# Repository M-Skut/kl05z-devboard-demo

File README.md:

# KL-05 DevBoard Demo project with simple HAL

## Hardware
To make development of advanced microcontroller projects simple, the DevBoard is equipped with following features:
- SD Card slot
- 6-button keypad connected as analog input
- stylophone-like keyboard as analog input
- PMOD Interface Type 2 (SPI)
- MikroBus Connector
- 3x WS2812B addressable RGB LEDs
- connector for Nokia 5510 display board
- buzzer
- fused 3V3 and 5V lines
- connector for Adafruit ALS-PT19 Analog Light Sensor Breakout
- connector for 16x2 LCD with I2C adapter
- 25LCxxx SPI Flash
- 2x 24Cxx I2C Flash
- RTC clock with battery based on PCF8563 RTC IC with I2C interface
- LM75 I2C temperature sensor

## Some photos of the hardware (more in `media` folder)

## Bill Of Materials
Interactive Bill Of Materials for the newest revision of the hardware can be found [here](frdm05-devboard-hardware/bom/ibom.html)

#### Hardware revision history
Rev. 1:
- first revision of hardware
Rev. 2:
- fix for analog keypad (wrong placement of current mirror)
- addition of current-limiting resistor for buzzer
- addition of optional fuses for 3V3 and 5V lines
Rev. 2.1:
- fix for 3V3 fuse
- fix for buzzer footprint
- fix for some silkscreen areas
Rev. 2.2:
- change 74HCT1G125GV buffer to faster 74AHCT1G125GV version

## Environment
To develop this demonstration project, following set of tools and programs was used:
- [Visual Studio Code](https://code.visualstudio.com/) with plugins:
    - [`Cortex Debug`](https://marketplace.visualstudio.com/items?itemName=marus25.cortex-debug) from `marus25`
    - [`CMake Tools`](https://marketplace.visualstudio.com/items?itemName=ms-vscode.cmake-tools) from `microsoft`
- GNU GCC ARM Compiler from Official ARM Distribution
- SEGGER JLINK
- CMake
- Ninja
- (Optional) ARM Compiler 5 from Keil
- (Optional) Doxygen

### How to install it on Windows
- Install GCC from [Official ARM Distribution](https://developer.arm.com/tools-and-software/open-source-software/developer-tools/gnu-toolchain/gnu-rm/downloads) and **check "Add to PATH"** when installing
- Install [CMake](https://cmake.org/download/), also **Add to PATH** when installing
- Install [J-Link Software and Documentation pack](https://www.segger.com/downloads/jlink/)
- Download [Ninja](https://github.com/ninja-build/ninja/releases) and put it into some folder in PATH, for example in `C:\Program Files\CMake\bin`
- [Install Visual Studio Code](https://code.visualstudio.com/download) and its extensions
- (Optional) Install [Doxygen](https://www.doxygen.nl/download.html) for generating documentation

### How to install it on other operating systems
- Install the required software from author's website or from OS repositories.

Now you can open the project folder. Select GNU toolchain as CMake kit when asked and edit file `launch.json` inside `.vscode` folder if your `JLinkGDBServer` location is different than he one used in this project. For ARM Compiler 5.06 toolchain,
an environment variable `ARMCC_TOOLCHAIN_PATH` has to be set to `bin` folder of the toolchain files. Alternatively, `armcc.cmake` file inside `toolchain-conf` can be edited to make te path setting permanent.

### Environment features
- two-click switch between ARM Compiler 5 and GCC Compiler
- all code editing features that Visual Studio Code has to offer
- easy debugging of compiled code
- two-click generation of doxygen HTML documentation
- built-in git integration
- works on Windows, GNU/Linux and Mac OS (or at least should)

## HAL
This simple hardware abstraction layer is based on two sources: KL05 Sample Code Package
from Freescale and MBED platform-specific code for KLXX targets. The C API relies
on heavy use of custom enums and structs to ensure that invalid function parameters can be found in
compilation stage. It uses C99 features (`stdint.h`, `stdbool.h`, in-place struct 
initialization etc.) and was tested with GCC 11 compiler and ARM 5.06 Compiler, but should
be compiler-independent, as it does not use compiler-dependent features directly, but instead it's using
CMSIS functions as abstraction layer.

### Goals:
- Prevent user from error-prone and hard-to-debug manual peripheral register setting
- Simple and straightforward for both understanding the underlying code and using the API
- Versatile - use for all applications within this uC
- Smallish footprint
- Separated device drivers from mcu peripheral drivers (exceptions only for very timing-sensitive devices)
- User-proof, mostly
- Peripherals can be reinitialized and will still work
- Communication peripheral drivers can be used without gpio driver
- Supports any MCU working frequency 

### Non-goals:
- universal
- unified (in GPIO mapping, same peripheral but more instances etc.)

### Drivers features:
#### UART:
- different pinout configuration
- automatic calculation for baudrate with ability to re-init if CPU speed changes
- error if configuration baudrate or pins cannot be set
- simple print, putchar and getchar API
- RX IRQ callback setting and checking RX overrun

#### I2C:
- different pinout configuration
- different speed selection
- timeout detection in all functions
- included fix for silicon errata
  
#### GPIO
- bare-bones abstraction of the register setting
- interrupt with callback functions
- inline functions for fast pin setting

#### Delay
- SysTick-based delay
- works without affecting SysTick settings
- based on delay code from u8g2 project

#### ADC
- ADC calibration function
- simple 16-bit value read
- uses `gpio` driver for pin mapping
- ADC presets (currently only one available)

#### PWM
- TPM-based PWM
- uses `gpio` driver for pin mapping
- allows setting period and pulse width in microseconds or as raw values

#### WS2812
- currently only GCC supported
- based on [cpldcpu's WS2812 ARM bitbang driver](https://github.com/cpldcpu/light_ws2812/blob/master/light_ws2812_ARM/light_ws2812_cortex.c)

#### MMA8451Q
- range setting
- conversion to float values

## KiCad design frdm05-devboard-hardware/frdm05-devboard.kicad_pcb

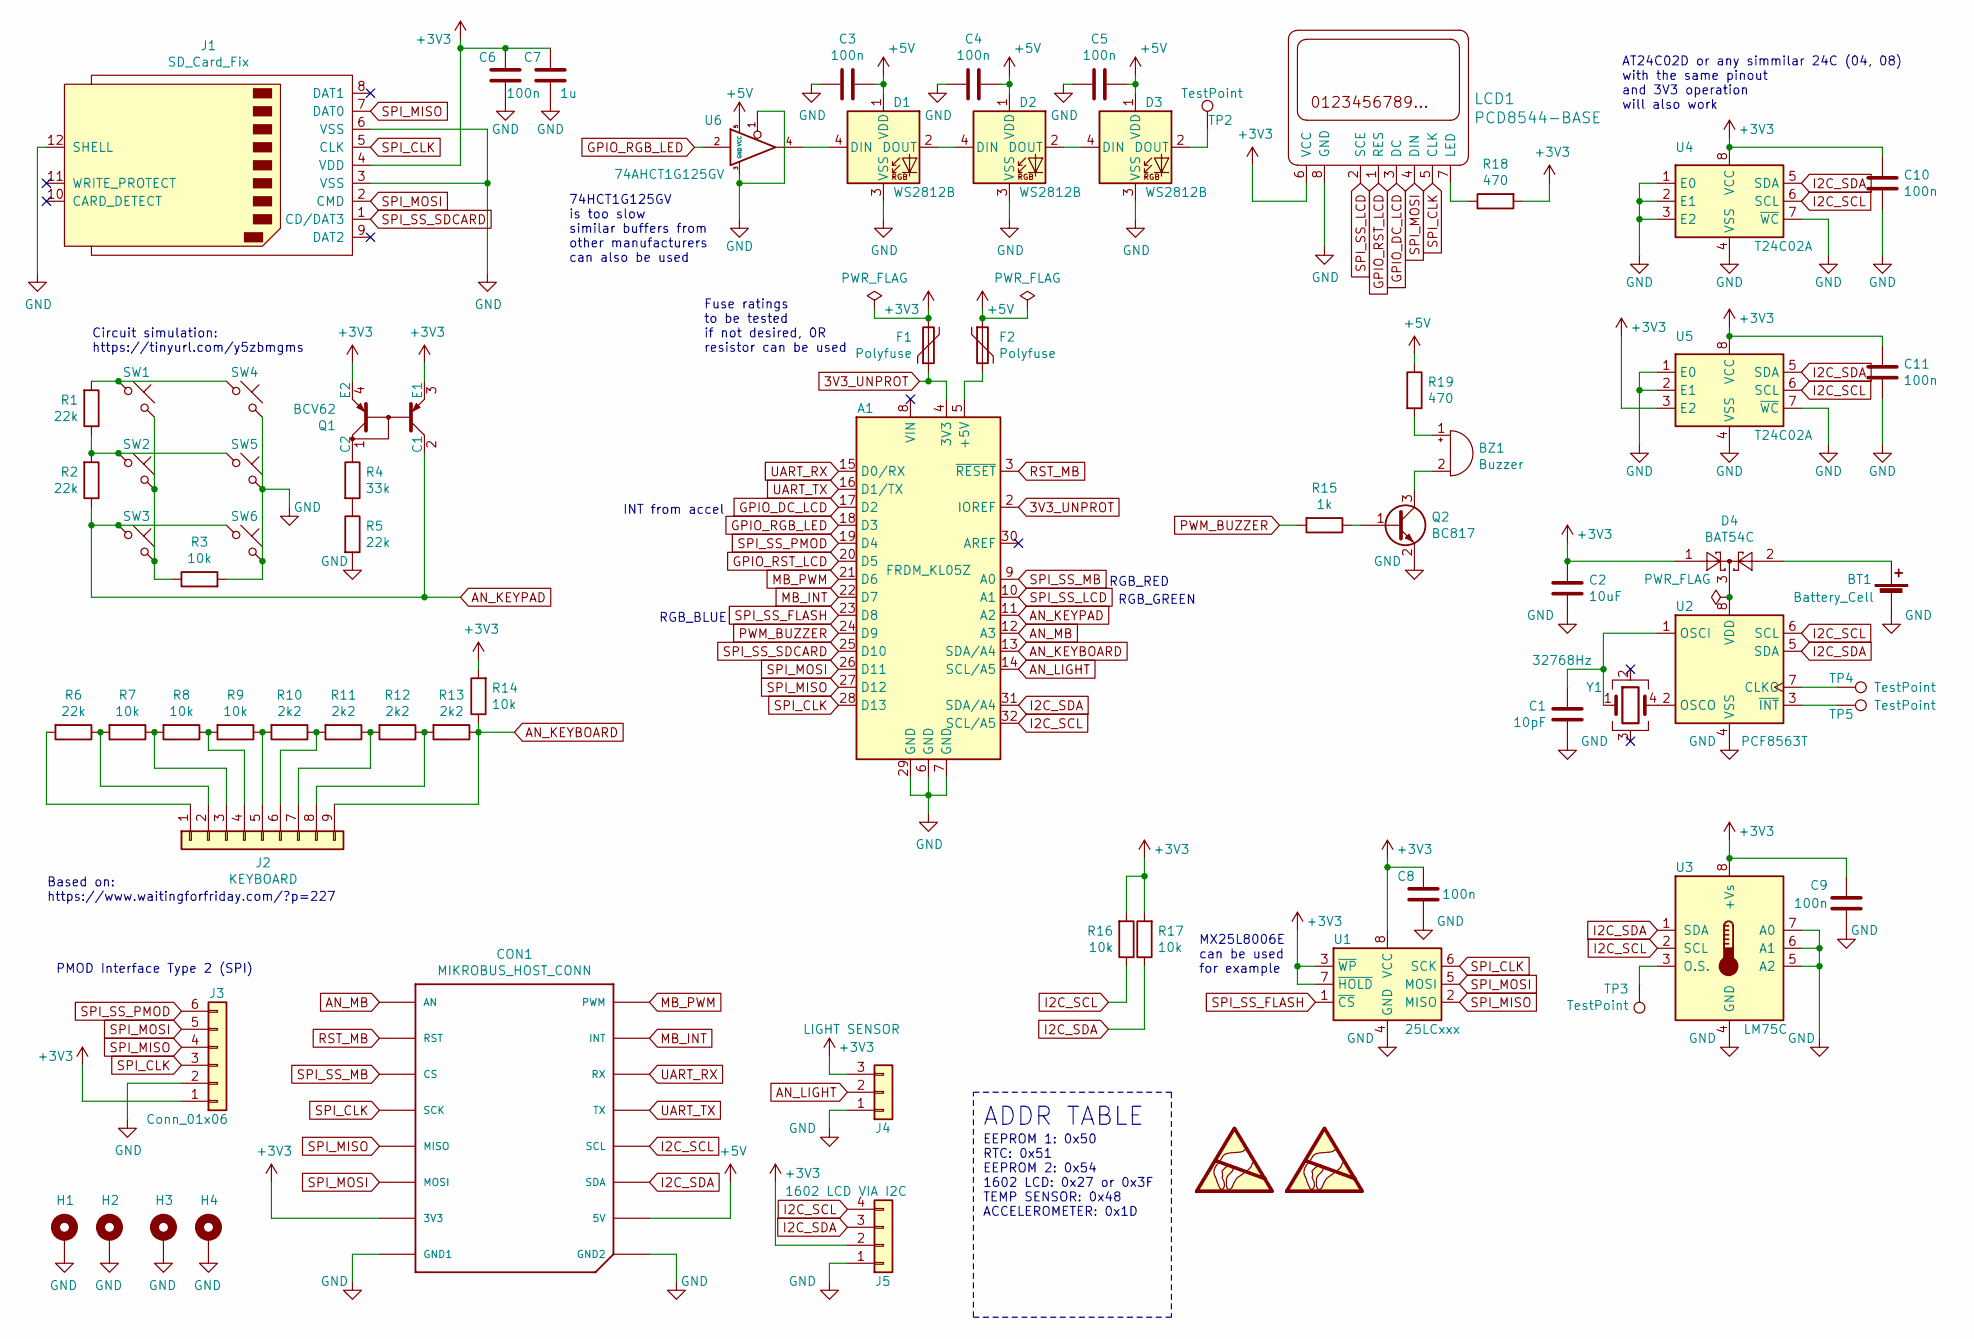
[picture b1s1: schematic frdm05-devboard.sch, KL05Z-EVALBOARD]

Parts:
A1: FRDM_KL05Z; FDRM-KL05Z
BT1: Battery_Cell; BatteryHolder_Keystone_1060_1x2032
BZ1: Buzzer; MagneticBuzzer_ProSignal_ABT-410-RC
C1: 10pF; C_0805_2012Metric_Pad1.18x1.45mm_HandSolder
C2: 10uF; C_0805_2012Metric_Pad1.18x1.45mm_HandSolder
C3, C4, C5, C6, C8, C9, C10, C11: 100n; C_0805_2012Metric_Pad1.18x1.45mm_HandSolder
C7: 1u; C_0805_2012Metric_Pad1.18x1.45mm_HandSolder
CON1: MIKROBUS_HOST_CONN
D1, D2, D3: WS2812B; LED_WS2812B_PLCC4_5.0x5.0mm_P3.2mm
D4: BAT54C; SOT-23
F1, F2: Polyfuse; Fuse_0805_2012Metric
H1, H2, H3, H4: MountingHole_Pad; MountingHole_3.2mm_M3_Pad_Via
J1: SD_Card_Fix; SD_TE_2041021
J2: KEYBOARD; Keyboard_resistive
J3: Conn_01x06; PinSocket_1x06_P2.54mm_Horizontal
J4: LIGHT SENSOR; PinSocket_1x03_P2.54mm_Vertical
J5: 1602 LCD VIA I2C; PinHeader_1x04_P2.54mm_Horizontal
LCD1: PCD8544-BASE; PinSocket_1x08_P2.54mm_Vertical
Q1: BCV62; SOT-143
Q2: BC817; SOT-23
R1, R2, R5, R6: 22k; R_0805_2012Metric_Pad1.20x1.40mm_HandSolder
R3, R7, R8, R9, R14, R16, R17: 10k; R_0805_2012Metric_Pad1.20x1.40mm_HandSolder
R4: 33k; R_0805_2012Metric_Pad1.20x1.40mm_HandSolder
R10, R11, R12, R13: 2k2; R_0805_2012Metric_Pad1.20x1.40mm_HandSolder
R15: 1k; R_0805_2012Metric_Pad1.20x1.40mm_HandSolder
R18, R19: 470; R_0805_2012Metric_Pad1.20x1.40mm_HandSolder
SW1, SW2, SW3, SW4, SW5, SW6: PTS810; SW_SPST_PTS810_HandSoldering
SYM1: SYM_ESD_Large; agieh
SYM2: SYM_ESD_Large; prestiz
TP2, TP3, TP4, TP5: TestPoint; TestPoint_THTPad_D2.0mm_Drill1.0mm
U1: 25LCxxx; SOIC-8_3.9x4.9mm_P1.27mm
U2: PCF8563T; SOIC-8_3.9x4.9mm_P1.27mm
U3: LM75C; SOIC-8_3.9x4.9mm_P1.27mm
U4, U5: T24C02A; SOIC-8_3.9x4.9mm_P1.27mm
U6: 74AHCT1G125GV; SOT-23-5_HandSoldering
Y1: 32768Hz; Crystal_SMD_SeikoEpson_MC306-4Pin_8.0x3.2mm_HandSoldering

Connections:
3V3_UNPROT: A1.2 (IOREF), A1.4 (3V3), F1.1
+3V3: C2.1, C6.2, C7.2, C8.1, C9.2, C10.2, C11.2, CON1.P7 (3V3), D4.1, F1.2, J1.4 (VDD), J3.1, J4.3, J5.2, LCD1.6 (VCC), Q1.3 (E1), Q1.4 (E2), R14.2, R16.2, R17.2, R18.2, U1.3 (~WP), U1.7 (~HOLD), U1.8 (VCC), U3.8 (+Vs), U4.8 (VCC), U5.3 (E2), U5.8 (VCC)
+5V: C3.1, C4.1, C5.1, CON1.P10 (5V), D1.1 (VDD), D2.1 (VDD), D3.1 (VDD), F2.1, R19.1, U6.5 (VCC)
AN_KEYBOARD: A1.13 (SDA/A4), J2.9, R13.1, R14.1
AN_KEYPAD: A1.11 (A2), Q1.2 (C1), R2.1, SW3.1, SW6.1
AN_LIGHT: A1.14 (SCL/A5), J4.2
AN_MB: A1.12 (A3), CON1.P1 (AN)
GND: A1.6 (GND), A1.7 (GND), A1.29 (GND), BT1.2 (-), C1.1, C2.2, C3.2, C4.2, C5.2, C6.1, C7.1, C8.2, C9.1, C10.1, C11.1, CON1.P8 (GND1), CON1.P9 (GND2), D1.3 (VSS), D2.3 (VSS), D3.3 (VSS), H1.1, H2.1, H3.1, H4.1, J1.3 (VSS), J1.6 (VSS), J1.12 (SHELL), J3.2, J4.1, J5.1, LCD1.8 (GND), Q2.2 (E), R3.2, R5.2, SW4.2, SW5.2, SW6.2, U1.4 (GND), U2.4 (VSS), U3.4 (GND), U3.5 (A2), U3.6 (A1), U3.7 (A0), U4.1 (E0), U4.2 (E1), U4.3 (E2), U4.4 (VSS), U4.7 (~WC), U5.1 (E0), U5.2 (E1), U5.4 (VSS), U5.7 (~WC), U6.1, U6.3 (GND)
GPIO_DC_LCD: A1.17 (D2), LCD1.3 (DC)
GPIO_RGB_LED: A1.18 (D3), U6.2
GPIO_RST_LCD: A1.20 (D5), LCD1.1 (RES)
I2C_SCL: A1.32 (SCL/A5), CON1.P12 (SCL), J5.4, R16.1, U2.6 (SCL), U3.2 (SCL), U4.6 (SCL), U5.6 (SCL)
I2C_SDA: A1.31 (SDA/A4), CON1.P11 (SDA), J5.3, R17.1, U2.5 (SDA), U3.1 (SDA), U4.5 (SDA), U5.5 (SDA)
MB_INT: A1.22 (D7), CON1.P15 (INT)
MB_PWM: A1.21 (D6), CON1.P16 (PWM)
unnamed: A1.5 (+5V), F2.2
unnamed: BT1.1 (+), D4.2
unnamed: BZ1.1 (-), R19.2
unnamed: BZ1.2 (+), Q2.3 (C)
unnamed: C1.2, U2.1 (OSCI), Y1.1
unnamed: D1.2 (DOUT), D2.4 (DIN)
unnamed: D1.4 (DIN), U6.4
unnamed: D2.2 (DOUT), D3.4 (DIN)
unnamed: D3.2 (DOUT), TP2.1
unnamed: D4.3, U2.8 (VDD)
unnamed: J2.1, R6.2
unnamed: J2.2, R6.1, R7.2
unnamed: J2.3, R7.1, R8.2
unnamed: J2.4, R8.1, R9.2
unnamed: J2.5, R9.1, R10.2
unnamed: J2.6, R10.1, R11.2
unnamed: J2.7, R11.1, R12.2
unnamed: J2.8, R12.1, R13.2
unnamed: LCD1.7 (LED), R18.1
unnamed: Q1.1 (C2), R4.1
unnamed: Q2.1 (B), R15.1
unnamed: R1.1, R2.2, SW2.1, SW5.1
unnamed: R1.2, SW1.1, SW4.1
unnamed: R3.1, SW1.2, SW2.2, SW3.2
unnamed: R4.2, R5.1
unnamed: TP3.1, U3.3 (O.S.)
unnamed: TP4.1, U2.7 (CLKO)
unnamed: TP5.1, U2.3 (~INT~)
unnamed: U2.2 (OSCO), Y1.4
PWM_BUZZER: A1.24 (D9), R15.2
RST_MB: A1.3 (~RESET), CON1.P2 (RST)
SPI_CLK: A1.28 (D13), CON1.P4 (SCK), J1.5 (CLK), J3.3, LCD1.5 (CLK), U1.6 (SCK)
SPI_MISO: A1.27 (D12), CON1.P5 (MISO), J1.7 (DAT0), J3.4, U1.2 (MISO)
SPI_MOSI: A1.26 (D11), CON1.P6 (MOSI), J1.2 (CMD), J3.5, LCD1.4 (DIN), U1.5 (MOSI)
SPI_SS_FLASH: A1.23 (D8), U1.1 (~CS)
SPI_SS_LCD: A1.10 (A1), LCD1.2 (SCE)
SPI_SS_MB: A1.9 (A0), CON1.P3 (CS)
SPI_SS_PMOD: A1.19 (D4), J3.6
SPI_SS_SDCARD: A1.25 (D10), J1.1 (CD/DAT3)
UART_RX: A1.15 (D0/RX), CON1.P14 (RX)
UART_TX: A1.16 (D1/TX), CON1.P13 (TX)

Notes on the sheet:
Circuit simulation: https://tinyurl.com/y5zbmgms
Based on: https://www.waitingforfriday.com/?p=227
AT24C02D or any simmilar 24C (04, 08) with the same pinout and 3V3 operation will also work
MX25L8006E can be used for example
ADDR TABLE
EEPROM 1: 0x50 RTC: 0x51 EEPROM 2: 0x54 1602 LCD: 0x27 or 0x3F TEMP SENSOR: 0x48 ACCELEROMETER: 0x1D
RGB_RED
RGB_GREEN
RGB_BLUE
INT from accel
PMOD Interface Type 2 (SPI)
Fuse ratings to be tested if not desired, 0R resistor can be used
74HCT1G125GV is too slow similar buffers from other manufacturers can also be used

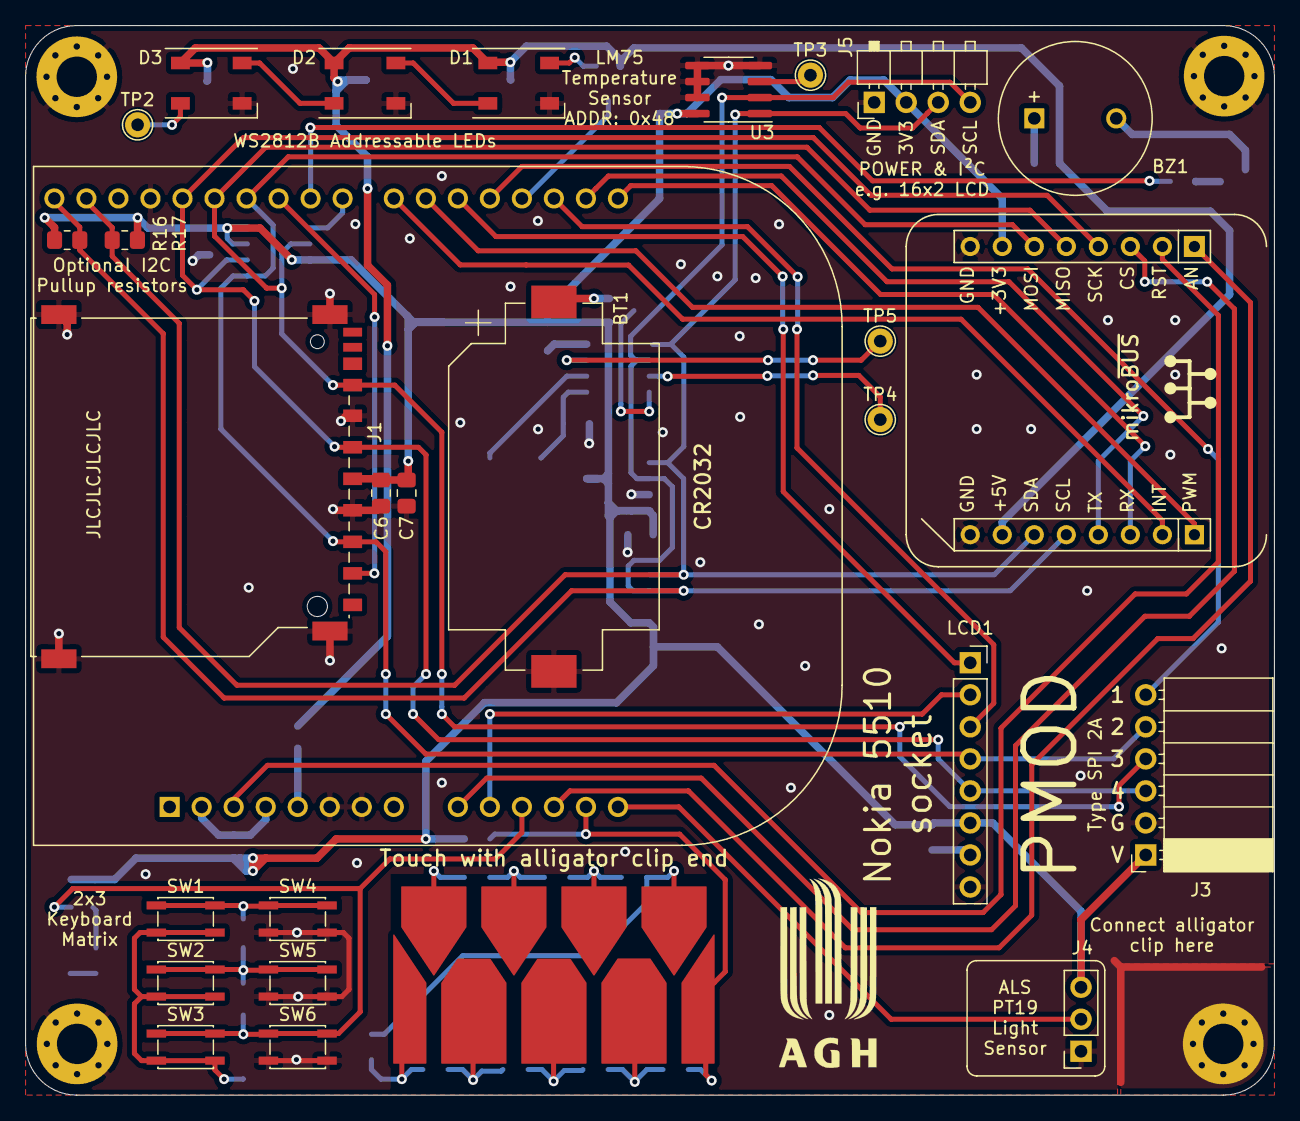
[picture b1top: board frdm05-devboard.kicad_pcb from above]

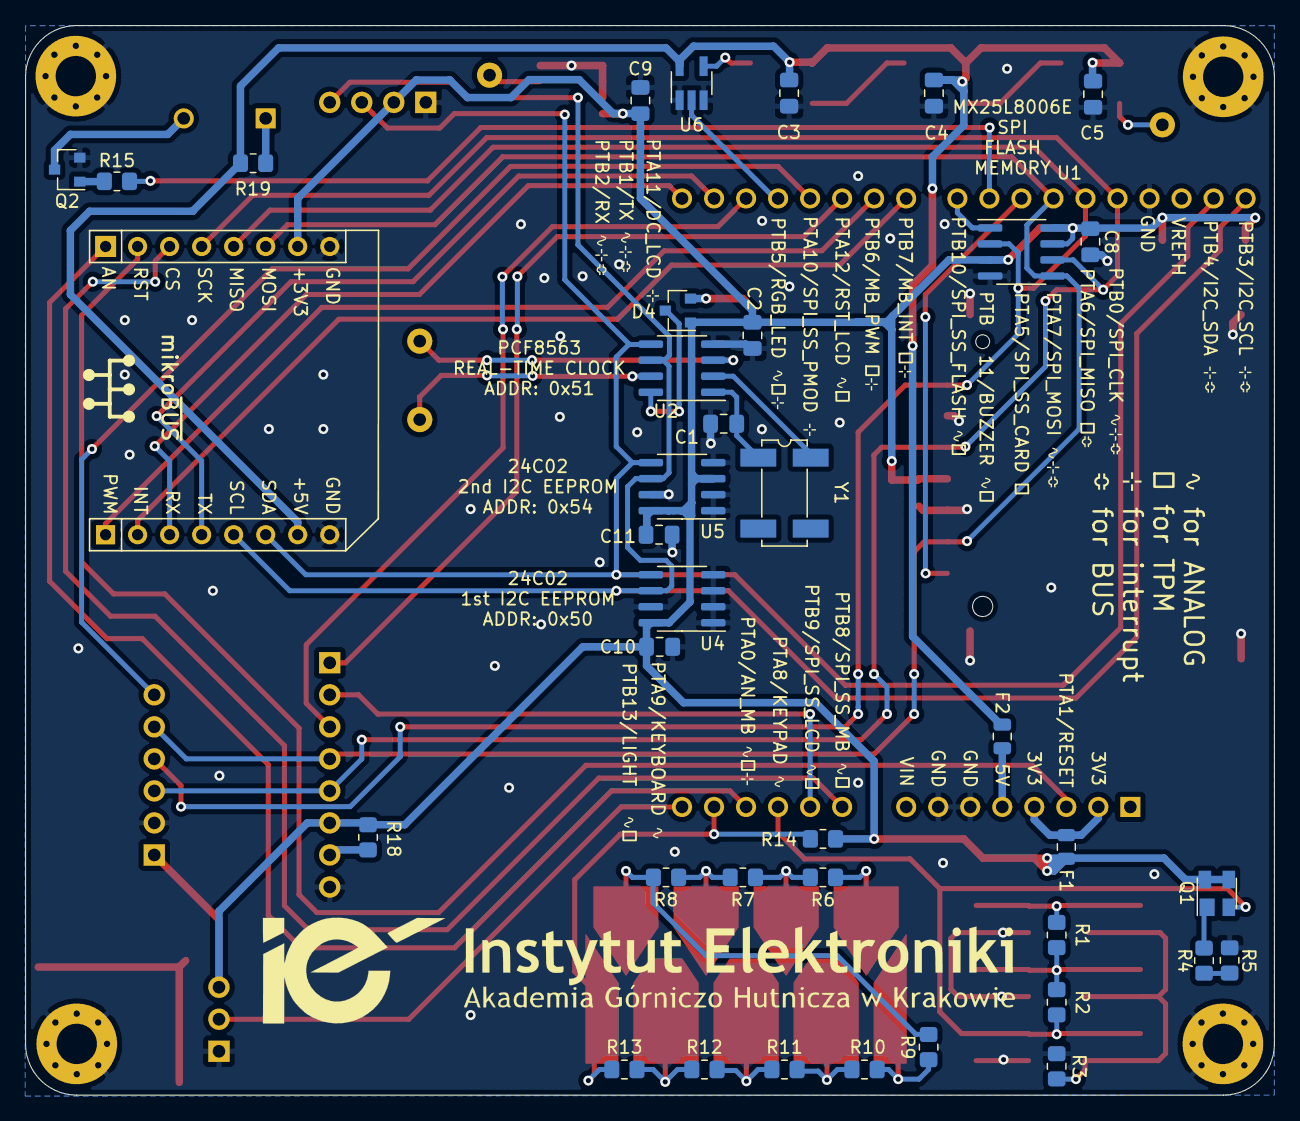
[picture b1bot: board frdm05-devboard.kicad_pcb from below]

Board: 2 copper layers, 99.1 x 84.8 mm, 71 parts (38 on the bottom side), 56 nets.

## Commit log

2022-01-17 Initial commit of work-in-progress firmware
2022-01-19 Initial commit of Rev.1 hardware
2022-01-19 Initial commit of Rev.2 hardware
2022-01-19 Regenerate IBOM for Rev. 2
2022-01-20 Added .gitattributes
2022-01-20 Fix .gitattributes
2022-01-20 Initial commit of Rev.2.1 hardware
2022-01-20 Initial commit of Rev.2.2 hardware
2022-01-20 Add notes about Rev. 2.2
2022-01-20 Change default microrl config and integrate it instead of using submodule
2022-01-20 Add description for other drivers
2022-01-21 Fix note about using alternative buffer for WS2812B LEDs
2022-01-22 Added photos of Rev. 1 PCB
